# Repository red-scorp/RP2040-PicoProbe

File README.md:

```
 ______ ______ ______ ______ _____  ______
|   __ \   __ \__    |      |  |  ||      |
|      <    __/    __|  --  |__    |  --  |
|___|__|___|  |______|______|  |__||______|
 ______ __              ______              __
|   __ \__|.----.-----.|   __ \.----.-----.|  |--.-----.
|    __/  ||  __|  _  ||    __/|   _|  _  ||  _  |  -__|
|___|  |__||____|_____||___|   |__| |_____||_____|_____|
```

# RP2040-PicoProbe Project

The **RP2040-PicoProbe** project aims to create even smaller version of RP2040-DebugProbe.

## RP2040-PicoProbe Board

The **RP2040-PicoProbe** board is a 4-layer design intended to accommodate the popular Raspberry Pi RP2040 MCU with all required component to function identically to Raspberry Pi Debug Probe.

This board features target debug connector and PC host micro-USB connector.The board is pin-compatible with Raspberry Pi Debug Probe and can be used with the same picoprobe SW.

Preview:

You can view the [Schematics in PDF format](doc/RP2040-PicoProbe.pdf) for detailed information.

STEP 3D file is available [with pins](doc/RP2040-PicoProbe.step).

Features:

- Very small form-factor of about 28x13mm, about 37x13mm with pins.
- Raspberry Pi RP2040 MCU as a heart of the board.
- 2x8 2.54mm SWD/UART/Power connector for programming and debugging.
- Micro USB connector for power and communication.
- Several LEDs to indicate power and status.
- Castellated holes connector for main MCU debugging.
- BOOTSEL button to enter the bootloader mode for flashing new picoprobe SW.
- Pin-compatible with Raspberry Pi Debug Probe.
- Double-sided assembly.

CAM files, as well as the BOM and CPL files for JLCPCB, are available.

## Version History

### v1.0b1

Initial release for testing purposes.

## Links

- [Raspberry Pi RP2040 information page](https://www.raspberrypi.com/documentation/microcontrollers/rp2040.html).
- [Raspberry Pi Debug Probe information page](https://www.raspberrypi.com/documentation/microcontrollers/debug-probe.html).
- [Picoprobe SW for the board](https://github.com/raspberrypi/picoprobe).

## How to Help

Your contributions as code, resources, or finances are welcome! Please contact me directly via email at andriy.golovnya@gmail.com or through my [GitHub profile](https://github.com/red-scorp).

If you'd like to make a financial contribution, you can donate via [PayPal](http://paypal.me/redscorp) or [Ko-Fi](http://ko-fi.com/redscorp). Your support is greatly appreciated.

Thanks in advance!

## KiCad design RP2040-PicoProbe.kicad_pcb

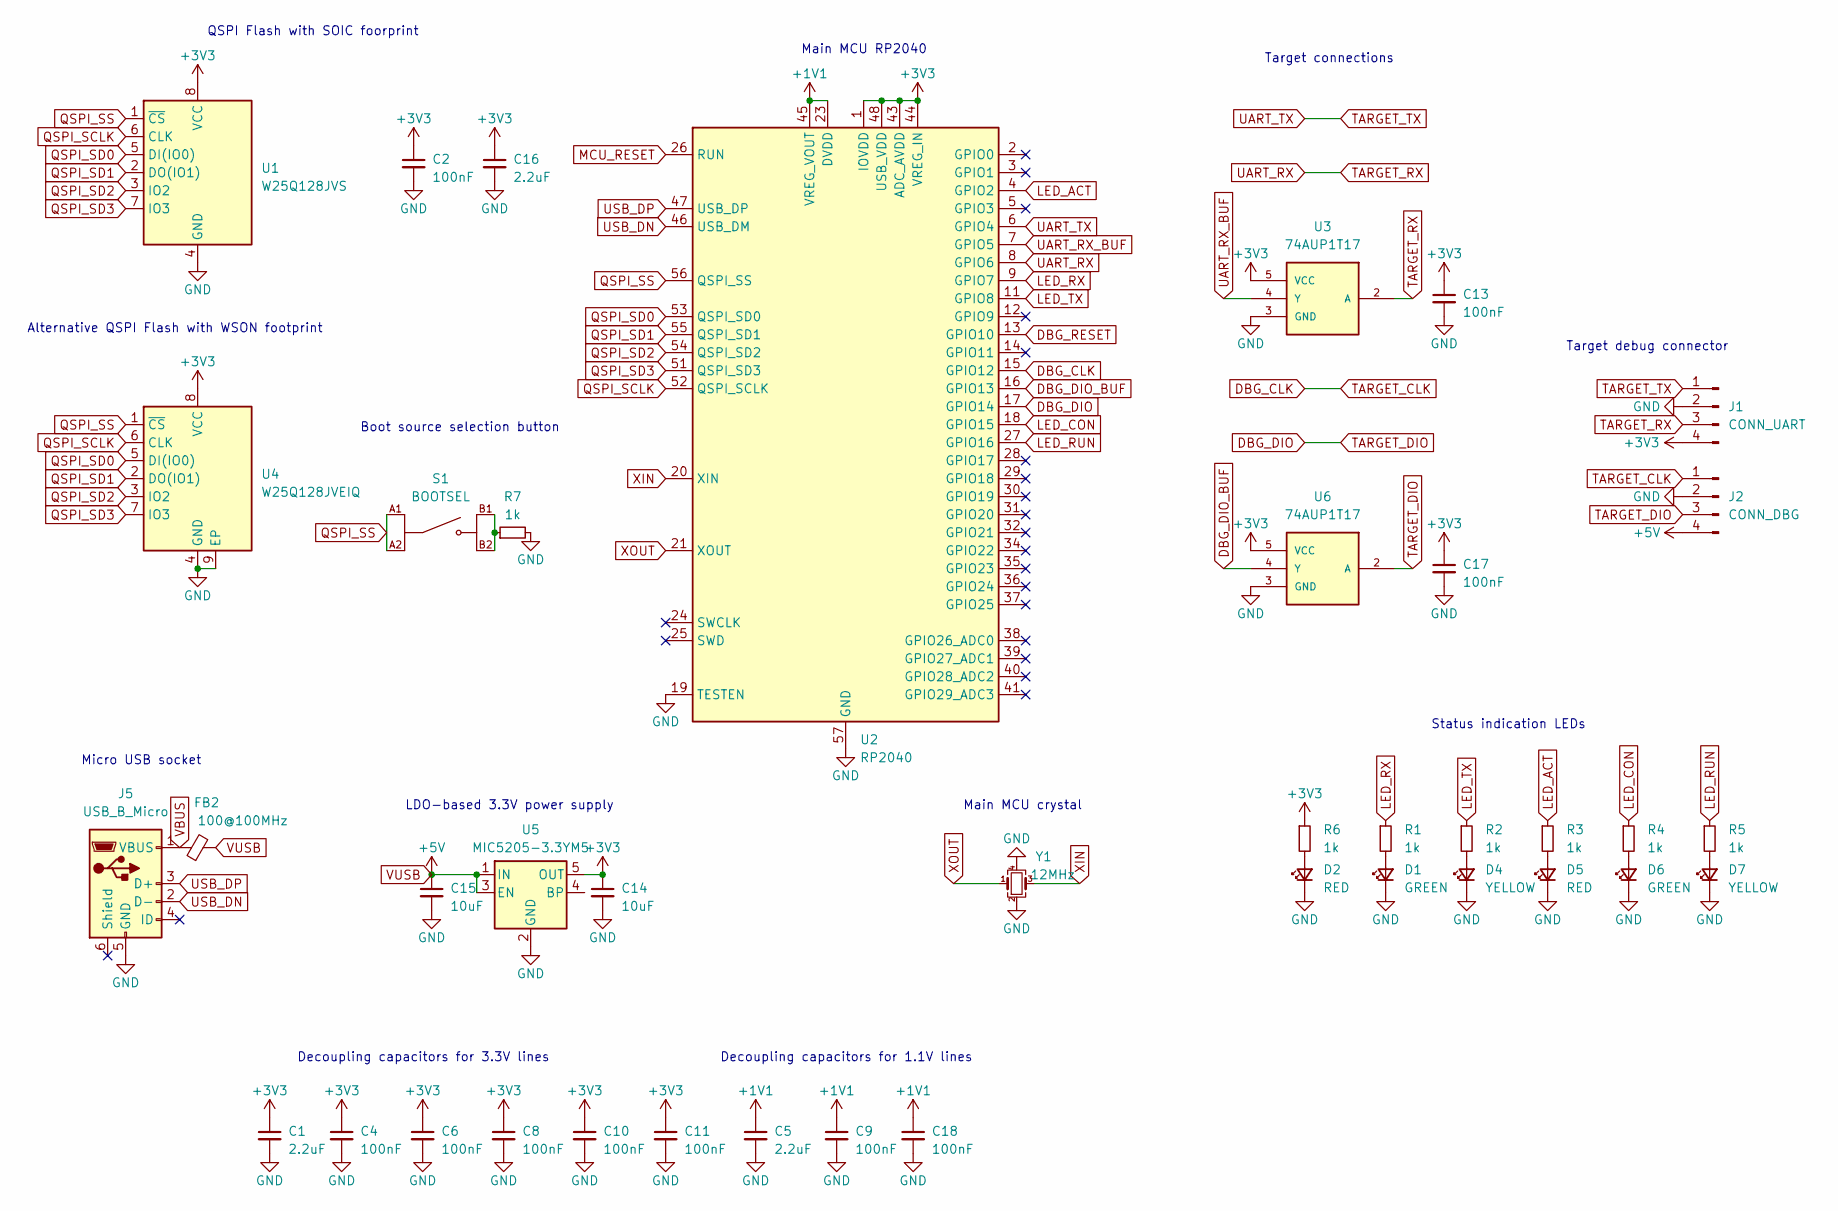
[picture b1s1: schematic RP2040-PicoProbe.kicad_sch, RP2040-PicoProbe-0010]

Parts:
C1, C5, C16: 2.2uF; C_0603_1608Metric
C2, C4, C6, C8, C9, C10, C11, C13, C17, C18: 100nF; C_0402_1005Metric
C14, C15: 10uF; C_0805_2012Metric
D1, D6: GREEN; LED_0603_1608Metric
D2, D5: RED; LED_0603_1608Metric
D4, D7: YELLOW; LED_0603_1608Metric
FB2: 100@100MHz; L_0805_2012Metric
J1: CONN_UART; Harwin_M20-89004xx_1x04_P2.54mm_Horizontal
J2: CONN_DBG; Harwin_M20-89004xx_1x04_P2.54mm_Horizontal
J5: USB_B_Micro; USB_Micro-B_Molex_47346-0001
R1, R2, R3, R4, R5, R6, R7: 1k; R_0402_1005Metric
S1: BOOTSEL; SW_EVPBB0AAB000; DIGI-KEY_PART_NUMBER P19888CT-ND
U1: W25Q128JVS; SOIC-8_5.23x5.23mm_P1.27mm
U2: RP2040; QFN-56-1EP_7x7mm_P0.4mm_EP3.2x3.2mm
U3, U6: 74AUP1T17; SOT-353_SC-70-5
U4: W25Q128JVEIQ; WSON-8-1EP_6x5mm_P1.27mm_EP3.4x4.3mm
U5: MIC5205-3.3YM5; SOT-23-5
Y1: 12MHz; Crystal_SMD_3225-4Pin_3.2x2.5mm

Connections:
+1V1: C5.1, C9.1, C18.1, U2.23 (DVDD), U2.45 (VREG_VOUT), U2.50 (DVDD)
+3V3: C1.1, C2.1, C4.1, C6.1, C8.1, C10.1, C11.1, C13.1, C14.1, C16.1, C17.1, J1.4, R6.1, U1.8 (VCC), U2.1 (IOVDD), U2.10 (IOVDD), U2.22 (IOVDD), U2.33 (IOVDD), U2.42 (IOVDD), U2.43 (ADC_AVDD), U2.44 (VREG_IN), U2.48 (USB_VDD), U2.49 (IOVDD), U3.5 (VCC), U4.8 (VCC), U5.5 (OUT), U6.5 (VCC)
DBG_CLK: J2.1, U2.15 (GPIO12)
DBG_DIO: J2.3, U2.17 (GPIO14), U6.2 (A)
DBG_DIO_BUF: U2.16 (GPIO13), U6.4 (Y)
DBG_RESET: U2.13 (GPIO10)
GND: C1.2, C2.2, C4.2, C5.2, C6.2, C8.2, C9.2, C10.2, C11.2, C13.2, C14.2, C15.2, C16.2, C17.2, C18.2, D1.1 (K), D2.1 (K), D4.1 (K), D5.1 (K), D6.1 (K), D7.1 (K), J1.2, J2.2, J5.5 (GND), R7.2, U1.4 (GND), U2.19 (TESTEN), U2.57 (GND), U3.3 (GND), U4.4 (GND), U4.9 (EP), U5.2 (GND), U6.3 (GND), Y1.2, Y1.4
LED_ACT: R3.1, U2.4 (GPIO2)
LED_CON: R4.1, U2.18 (GPIO15)
LED_RUN: R5.1, U2.27 (GPIO16)
LED_RX: R1.1, U2.9 (GPIO7)
LED_TX: R2.1, U2.11 (GPIO8)
MCU_RESET: U2.26 (RUN)
unnamed: D1.2 (A), R1.2
unnamed: D2.2 (A), R6.2
unnamed: D4.2 (A), R2.2
unnamed: D5.2 (A), R3.2
unnamed: D6.2 (A), R4.2
unnamed: D7.2 (A), R5.2
unnamed: R7.1, S1.B1, S1.B2
QSPI_SCLK: U1.6 (CLK), U2.52 (QSPI_SCLK), U4.6 (CLK)
QSPI_SD0: U1.5 (DI(IO0)), U2.53 (QSPI_SD0), U4.5 (DI(IO0))
QSPI_SD1: U1.2 (DO(IO1)), U2.55 (QSPI_SD1), U4.2 (DO(IO1))
QSPI_SD2: U1.3 (IO2), U2.54 (QSPI_SD2), U4.3 (IO2)
QSPI_SD3: U1.7 (IO3), U2.51 (QSPI_SD3), U4.7 (IO3)
QSPI_SS: S1.A1, S1.A2, U1.1 (~CS), U2.56 (QSPI_SS), U4.1 (~CS)
TARGET_RX: J1.3, U2.8 (GPIO6), U3.2 (A)
TARGET_TX: J1.1, U2.6 (GPIO4)
UART_RX_BUF: U2.7 (GPIO5), U3.4 (Y)
USB_DN: J5.2 (D-), U2.46 (USB_DM)
USB_DP: J5.3 (D+), U2.47 (USB_DP)
VBUS: FB2.1, J5.1 (VBUS)
VUSB: C15.1, FB2.2, J2.4, U5.1 (IN), U5.3 (EN)
XIN: U2.20 (XIN), Y1.3
XOUT: U2.21 (XOUT), Y1.1

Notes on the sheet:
Alternative QSPI Flash with WSON footprint
Main MCU RP2040
Status indication LEDs
Decoupling capacitors for 3.3V lines
Main MCU crystal
Decoupling capacitors for 1.1V lines
Target connections
Target debug connector
Micro USB socket
Boot source selection button
LDO-based 3.3V power supply
QSPI Flash with SOIC foorprint

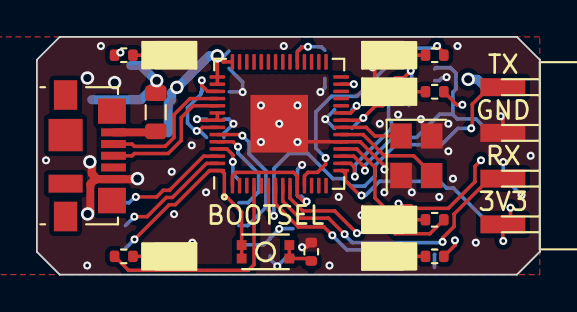
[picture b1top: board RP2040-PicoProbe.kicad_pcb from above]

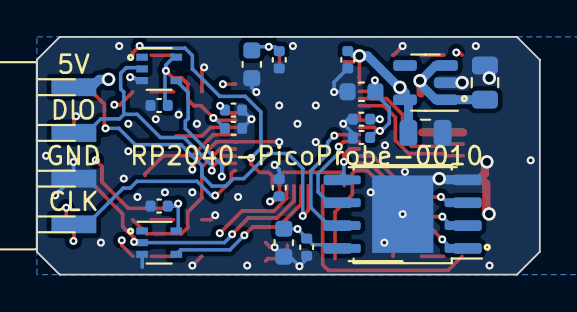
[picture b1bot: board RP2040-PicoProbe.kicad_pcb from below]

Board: 4 copper layers, 27.9 x 13.2 mm, 40 parts (21 on the bottom side), 33 nets.

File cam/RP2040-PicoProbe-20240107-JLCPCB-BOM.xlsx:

Qty | Designator | Footprint | JLCPCB Part# | Designation
2 | D7,D4 | 0603 | C72038 | YELLOW
1 | FB2 | 0805 | C1015 | GZ2012D101TF
2 | D2,D5 | 0603 | C2286 | RED
1 | J5 | SMD | C2763165 | USB_B_Micro
1 | U2 | LQFN-56(7x7) | C2040 | RP2040
7 | R3,R7,R5,R1,R6,R4,R2 | 0402 | C11702 | 1k
1 | S1 | SMD,1.6x2.6mm | C913786 | 1TS026A-1800-0553-CT
2 | D1,D6 | 0603 | C72043 | GREEN
1 | Y1 | SMD3225-4P | C9002 | 12MHz
10 | C4,C11,C9,C17,C13,C18,C2,C6,C10,C8 | 0402 | C1525 | 100nF
3 | C5,C1,C16 | 0603 | C1604 | 2.2uF
2 | U3,U6 | SC-70-5 | C2652100 | 74AUP1T17
2 | C14,C15 | 0805 | C15850 | 10uF
1 | U1 | SOIC-8-208mil | C97521 | W25Q128JVS
1 | U5 | SOT-23-5 | C37970 | MIC5205-3.3YM5
1 | U4 | WSON-8-EP(6x8) | C2456297 | W25Q128JVEIQ

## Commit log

2024-01-05 Used RP2040-MicroProbe files as base for the board.
2024-01-05 Renamed schematic and board title
2024-01-05 Removed host debug part. Moved secondary components to the back of the board.
2024-01-05 Roughly put components to their places
2024-01-06 Made the board smaller. Organized components to their expected locations.
2024-01-06 Added traces between components
2024-01-06 Moved stuff around
2024-01-06 Generated PNG preview
2024-01-06 Generated PDF schematics
2024-01-06 Generated STEP 3D model
2024-01-06 Generated CAM files
2024-01-07 Generated generic BOM and CPL files
2024-01-07 Generated BOM and CPL files
2024-01-07 Some KiCad stuff
2024-01-07 Added b1 preview
2024-01-07 Rotated few components

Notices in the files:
RP2040-PicoProbe.kicad_pcb:
(c) 2024 Andriy Golovnya
